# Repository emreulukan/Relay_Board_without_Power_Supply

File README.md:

# Relay_Board_without_Power_Supply

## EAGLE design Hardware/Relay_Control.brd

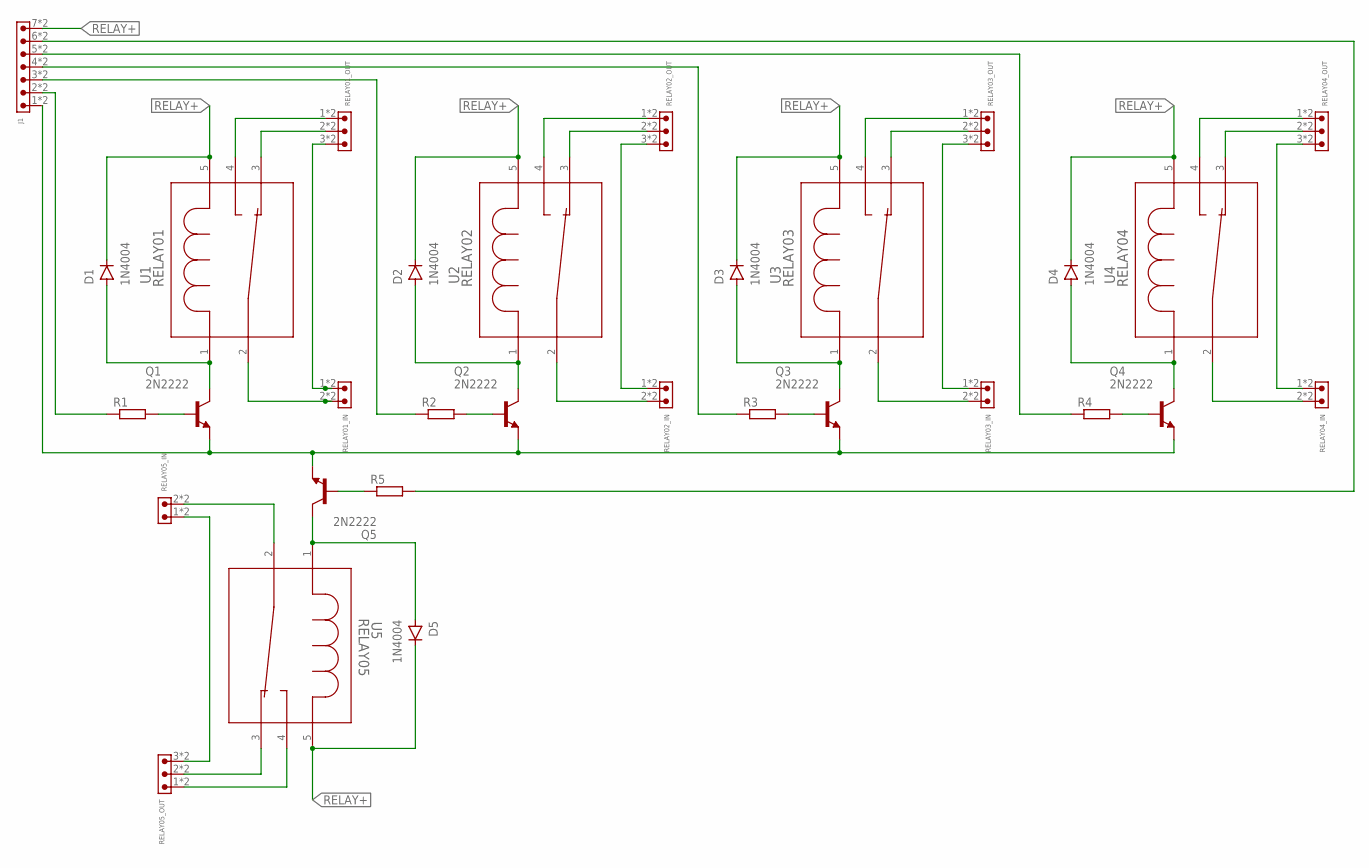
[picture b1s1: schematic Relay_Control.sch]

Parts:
D1, D2, D3, D4, D5: 1N4004; DO-41
J1: 638263222007
Q1, Q2, Q3, Q4, Q5: 2N2222; TO18
R1, R2, R3, R4, R5: R-EU_0207/10; 0207/10
RELAY01_IN, RELAY02_IN, RELAY03_IN, RELAY04_IN, RELAY05_IN: 638263222002
RELAY01_OUT, RELAY02_OUT, RELAY03_OUT, RELAY04_OUT, RELAY05_OUT: 638263222003
U1: RELAY01; RELAY-SPDT_3.2MM
U2: RELAY02; RELAY-SPDT_3.2MM
U3: RELAY03; RELAY-SPDT_3.2MM
U4: RELAY04; RELAY-SPDT_3.2MM
U5: RELAY05; RELAY-SPDT_3.2MM

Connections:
GND: J1.1, J1.A1 (1), Q1.1 (E), Q2.1 (E), Q3.1 (E), Q4.1 (E), Q5.1 (E)
unnamed: J1.4, J1.A4 (4), R3.1
unnamed: D1.A, Q1.3 (C), U1.1
unnamed: Q1.2 (B), R1.2
unnamed: J1.2, J1.A2 (2), R1.1
unnamed: RELAY01_IN.1, RELAY01_IN.A1 (1), RELAY01_OUT.3, RELAY01_OUT.A3 (3)
unnamed: RELAY01_OUT.1, RELAY01_OUT.A1 (1), U1.4
unnamed: RELAY01_OUT.2, RELAY01_OUT.A2 (2), U1.3
unnamed: J1.5, J1.A5 (5), R4.1
unnamed: RELAY01_IN.2, RELAY01_IN.A2 (2), U1.2
unnamed: D2.A, Q2.3 (C), U2.1
unnamed: Q2.2 (B), R2.2
unnamed: RELAY02_IN.1, RELAY02_IN.A1 (1), RELAY02_OUT.3, RELAY02_OUT.A3 (3)
unnamed: RELAY02_OUT.1, RELAY02_OUT.A1 (1), U2.4
unnamed: RELAY02_OUT.2, RELAY02_OUT.A2 (2), U2.3
unnamed: RELAY02_IN.2, RELAY02_IN.A2 (2), U2.2
unnamed: J1.3, J1.A3 (3), R2.1
unnamed: J1.6, J1.A6 (6), R5.2
unnamed: D3.A, Q3.3 (C), U3.1
unnamed: Q3.2 (B), R3.2
unnamed: RELAY03_IN.1, RELAY03_IN.A1 (1), RELAY03_OUT.3, RELAY03_OUT.A3 (3)
unnamed: RELAY03_OUT.1, RELAY03_OUT.A1 (1), U3.4
unnamed: RELAY03_OUT.2, RELAY03_OUT.A2 (2), U3.3
unnamed: RELAY03_IN.2, RELAY03_IN.A2 (2), U3.2
unnamed: D4.A, Q4.3 (C), U4.1
unnamed: Q4.2 (B), R4.2
unnamed: RELAY04_IN.1, RELAY04_IN.A1 (1), RELAY04_OUT.3, RELAY04_OUT.A3 (3)
unnamed: RELAY04_OUT.1, RELAY04_OUT.A1 (1), U4.4
unnamed: RELAY04_OUT.2, RELAY04_OUT.A2 (2), U4.3
unnamed: RELAY04_IN.2, RELAY04_IN.A2 (2), U4.2
unnamed: D5.A, Q5.3 (C), U5.1
unnamed: Q5.2 (B), R5.1
unnamed: RELAY05_IN.1, RELAY05_IN.A1 (1), RELAY05_OUT.3, RELAY05_OUT.A3 (3)
unnamed: RELAY05_OUT.1, RELAY05_OUT.A1 (1), U5.4
unnamed: RELAY05_OUT.2, RELAY05_OUT.A2 (2), U5.3
unnamed: RELAY05_IN.2, RELAY05_IN.A2 (2), U5.2
RELAY+: D1.C, D2.C, D3.C, D4.C, D5.C, J1.7, J1.A7 (7), U1.5, U2.5, U3.5, U4.5, U5.5

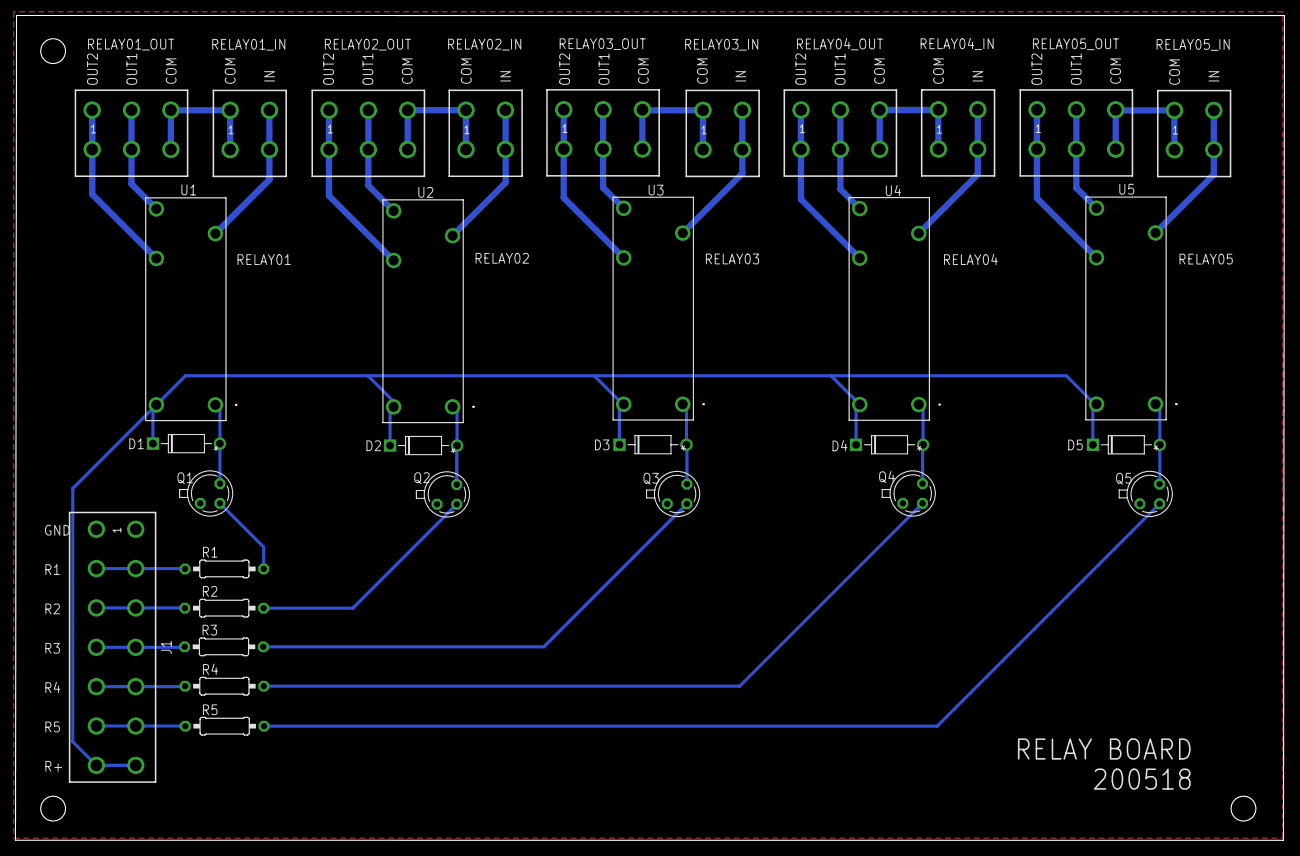
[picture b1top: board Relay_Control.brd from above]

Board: 2 copper layers, 163.8 x 106.5 mm, 31 parts (0 on the bottom side), 37 nets.

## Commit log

2020-05-18 Hardware

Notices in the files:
parts and their libraries:
Wurth_Connectors_WR-FAST: Copyright: Würth Elektronik
COPYRIGHT: Copyright (C) 2016 Accelerated Designs. All rights reserved
SparkFun-Aesthetics: Licensing: Creative Commons ShareAlike 4.0 International - https://creativecommons.org/licenses/by-sa/4.0
